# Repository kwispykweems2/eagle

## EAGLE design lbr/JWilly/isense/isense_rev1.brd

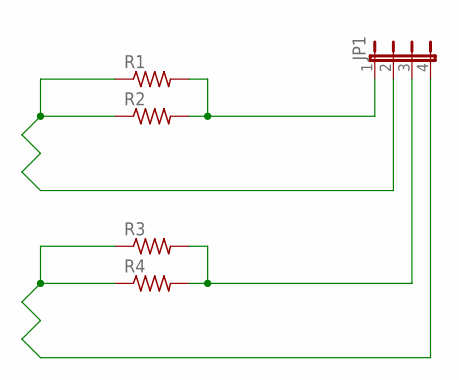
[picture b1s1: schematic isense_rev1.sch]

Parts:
JP1: JP4E; JP4
R1, R2, R3, R4: R-US_R0603; R0603

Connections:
COIL: JP1.2, R1.1, R2.1
COIL1: JP1.4, R3.1, R4.1
unnamed: JP1.3, R3.2, R4.2
unnamed: JP1.1, R1.2, R2.2

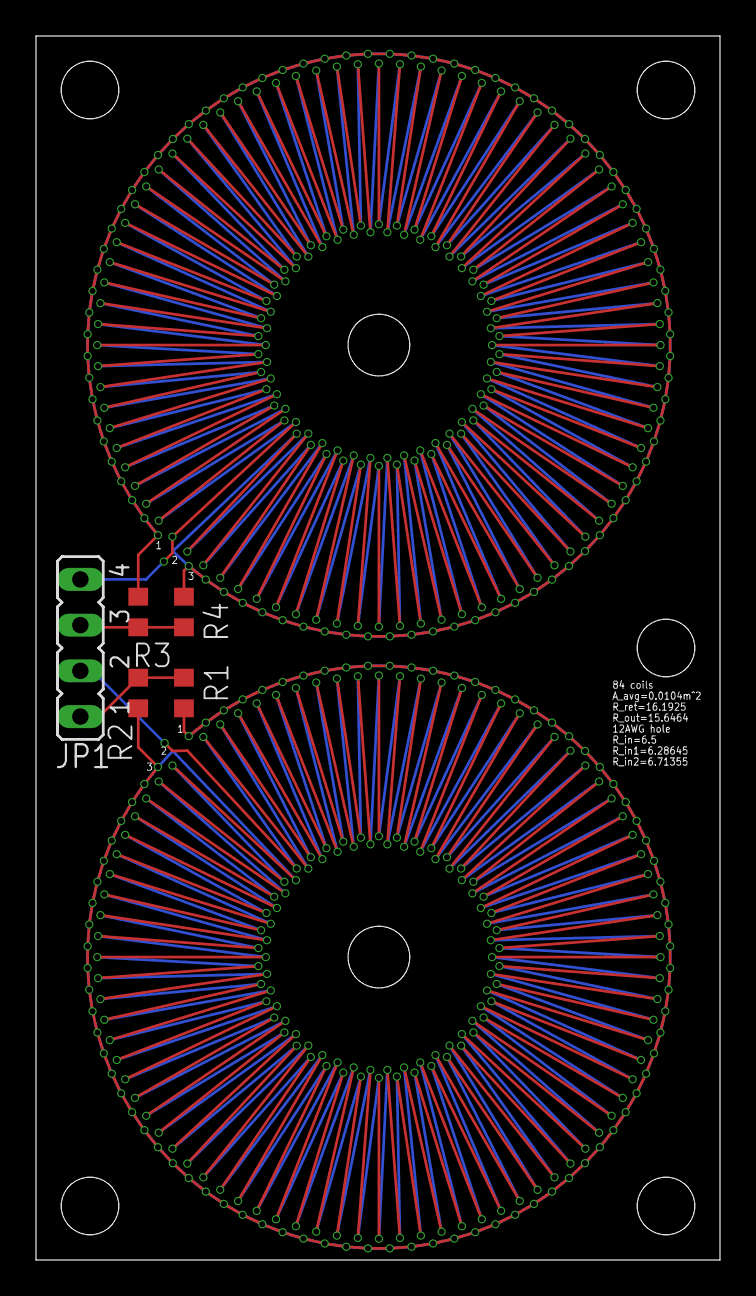
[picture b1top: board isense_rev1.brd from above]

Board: 2 copper layers, 38.0 x 68.0 mm, 5 parts (0 on the bottom side), 4 nets.

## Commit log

2016-04-28 first commit and upload
2016-04-28 Add Linux settings file
2016-06-08 Organize libraries into categories, half done.
2016-06-09 Finish categorizing libraries, add delete temp files script.
2016-06-15 Update for custom headers for pin1 square and pin1 circular.
2016-12-22 New libraries for VL53L0X sensor, info file for libraries
2016-12-29 Added 16MHz crystals and tactile switches.
